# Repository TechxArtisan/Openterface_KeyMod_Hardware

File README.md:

# Welcome to Openterface_KeyMod_Hardware

## Overview

The [Openterface KeyMod](https://openterface.com/keymod/) is a compact and portable open-source USB control gadget designed to turn your smartphone into a keyboard and mouse for a target device.

The KeyMod series includes two hardware variants, designed for different USB interfaces:

- KeyMod Mini: USB-C connector, with Bluetooth LE phone connectivity.
- KeyMod Plus: USB-A connector, with Bluetooth LE or wired USB phone connectivity.

Each variant provides hardware-based keyboard and mouse emulation. By connecting KeyMod to the target machine's USB port, users can control the system through the KeyCmd app without requiring Wi-Fi or additional software on the target.

This solution is particularly useful for developers, IT professionals, and hardware enthusiasts who work with computers, servers, Raspberry Pi boards, kiosks, and other USB-enabled devices.

## Hardware Features

The Openterface KeyMod PCB board comes with a variety of features designed to provide a seamless and efficient user experience:

- Compact Design: Small and portable form factor suitable for everyday carry.
- Multiple USB Variants: Available in USB-C and USB-A versions to support different target devices.
- Bluetooth Connectivity: Connects your smartphone to KeyMod for wireless control.
- Wired Connectivity: KeyMod Plus supports a wired USB connection to the controlling phone.
- USB HID Control: Emulates standard keyboard and mouse inputs, including in compatible BIOS/UEFI environments.
- USB Powered: Powered by the target device, with no battery required.
- Open Source: Hardware and software source materials are being published as the project evolves.
- [Community Support](https://forum.openterface.com/): Backed by an active open-source community.

## Firmware

KeyMod works with [Openterface_KM](https://github.com/TechxArtisanStudio/Openterface_KM), the keyboard and mouse emulation firmware used for target-side HID control in the Openterface ecosystem.

## Software

To use KeyMod, install the [KeyCmd app](https://openterface.com/keycmd/) on your smartphone.

Supported platforms include:

- [iOS](https://apps.apple.com/us/app/keycmd/id6776206628)
- [Android](https://openterface.com/keycmd/)

KeyCmd provides keyboard, touchpad, numpad, KM Pro, Compose & Send, presentation, gamepad, macro, and Terminal modes. Gamepad controls are mapped to standard keyboard and mouse input.

No additional software installation is required on the target for keyboard and mouse control. Simply connect KeyMod to a USB port that supports USB HID devices.

Terminal mode provides SSH access through KeyMod's network bridge on supported macOS and Linux targets, with an SSH service enabled.

## PCB Design

## license

- Hardware is released under CERN Open Hardware Licence Version 2 - Strongly Reciprocal
- Its softwares are released under GNU AFFERO GENERAL PUBLIC LICENSE Version 3
- Documentation is released under [CC BY-SA 4.0](https://creativecommons.org/licenses/by-sa/4.0/legalcode)

## Get Involved

Interested in contributing to the project? We welcome community involvement and contributions. For more information about getting involved, please visit the [Openterface Forum](https://forum.openterface.com/) or contact us directly.

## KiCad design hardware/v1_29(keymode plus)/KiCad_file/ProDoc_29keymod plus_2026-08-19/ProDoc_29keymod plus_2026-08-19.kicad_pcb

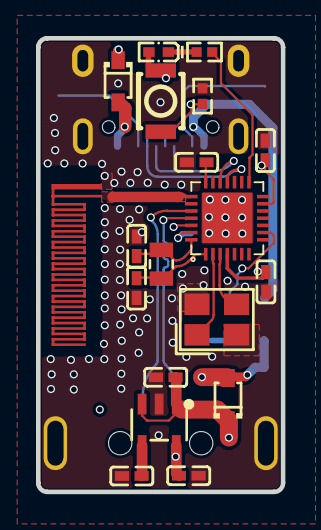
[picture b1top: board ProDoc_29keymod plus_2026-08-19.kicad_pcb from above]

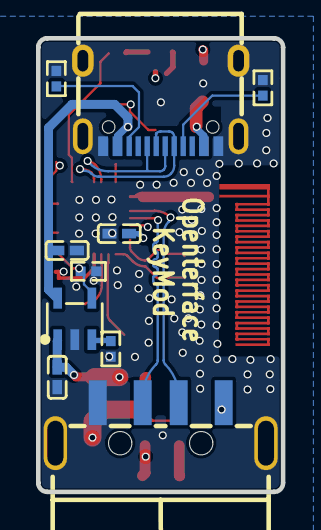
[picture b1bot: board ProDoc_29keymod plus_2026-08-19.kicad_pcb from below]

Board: 4 copper layers, 13.6 x 25.2 mm, 29 parts (10 on the bottom side), 22 nets.

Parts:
C1, C2, C11, C12, C13, C15, C17, C20, C25, C26, C27: C0402
D1, D3: SOD-323_L1.8-W1.3-LS2.5-RD
E2: ANT-F-2-2.4G-0.8mmFR4_1
LED1: LED_0402
R3, R4, R9, R20, R21, R22: R0402
SW1: KEY-SMD_B3U-1000PM
U2: QFN-28_L4.0-W4.0-P0.40-BL-EP2.8
U6, U25: SOT-23-5_L3.0-W1.7-P0.95-LS2.8-BL
USB1: USB-A-SMD_USB-212-BCW
USB2: USB-C-SMD_TYPE-C-16PIN-2MD-073
X1: CRYSTAL-SMD_2P-L2.0-W1.2
X3: CRYSTAL-SMD_4P-L3.2-W2.5-BL

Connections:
$1N1726: C13.1, U2.21
$1N1787: C25.2, U25.4
$1N12722: R20.2, U2.15
$1N14813: LED1.1, R20.1
$1N14821: R3.2, U6.3
BOOT0: R21.2, SW1.2, U2.26
CC21: R9.1, USB2.A5
CC22: R22.1, USB2.B5
DP1+: U2.25, USB1.3
DP1-: U2.24, USB1.2
DP2+: U2.19, USB2.A6, USB2.B6
DP2-: U2.18, USB2.A7, USB2.B7
GND: C1.1, C2.1, C11.1, C12.2, C13.2, C15.1, C17.1, C20.1, C25.1, C26.1, C27.1, R3.1, R4.2, R9.2, R21.1, R22.2, U2.29, U6.2, U25.2, USB1.4, USB1.5, USB2.13, USB2.14, USB2.A1B12, USB2.B1A12, X3.2, X3.4
OSCH_IN: U2.2, X3.1
OSCH_OUT: U2.3, X3.3
OSCL_IN: C1.2, U2.28, X1.2
OSCL_OUT: C2.2, U2.1, X1.1
V5: C27.2, D1.1, D3.1, U25.1, U25.3
V33: C15.2, C17.2, C20.2, C26.2, LED1.2, SW1.1, U2.4, U2.13, U2.27, U25.5
VIN1: C11.2, D1.2, U6.5, USB2.A4B9, USB2.B4A9
VIN2: C12.1, D3.2, U6.1, USB1.1
power: R4.1, U2.9, U6.4

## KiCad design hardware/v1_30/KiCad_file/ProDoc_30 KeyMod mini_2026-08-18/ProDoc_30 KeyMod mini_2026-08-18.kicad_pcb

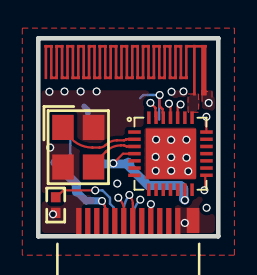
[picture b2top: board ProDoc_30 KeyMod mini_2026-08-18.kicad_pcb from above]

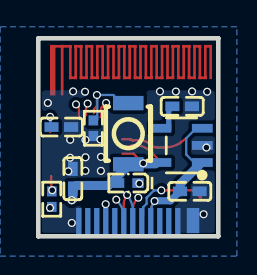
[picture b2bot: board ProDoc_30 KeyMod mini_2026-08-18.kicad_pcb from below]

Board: 4 copper layers, 10.0 x 11.0 mm, 14 parts (9 on the bottom side), 14 nets.

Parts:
C4, C13, C25, C27: C0402
E1: ANT-F-2-2.4G-0.8mmFR4_1
LED1: LED_0402
R1, R2, R21: R0402
SW1: KEY-SMD_B3U-1000PM
U1: USB-C-SMD_TYPE-C-24P-GTJB-040
U2: QFN-28_L4.0-W4.0-P0.40-BL-EP2.8
U25: SOT-23-5_L3.0-W1.7-P0.95-LS2.8-BL
X3: CRYSTAL-SMD_4P-L3.2-W2.5-BL

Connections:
$1N1726: C13.1, U2.21
$1N1787: C25.2, U25.4
$1N12770: LED1.1, R2.2
$1N12771: R2.1, U2.15
ANT: E1.1, U2.22
BOOT0: R21.2, SW1.2, U2.26
CC: R1.1, U1.B5
DP1+: U1.A6, U1.B6, U2.25
DP1-: U1.A7, U1.B7, U2.24
GND: C4.1, C13.2, C25.1, C27.1, E1.0, R1.2, R21.1, U1.25, U1.26, U1.A1, U1.A12, U1.B1, U1.B12, U2.29, U25.2, X3.2, X3.4
OSCH_IN: U2.2, X3.1
OSCH_OUT: U2.3, X3.3
V5: C27.2, U1.A4, U1.A9, U1.B4, U1.B9, U25.1, U25.3
V33: C4.2, LED1.2, SW1.1, U2.4, U2.13, U2.27, U25.5
